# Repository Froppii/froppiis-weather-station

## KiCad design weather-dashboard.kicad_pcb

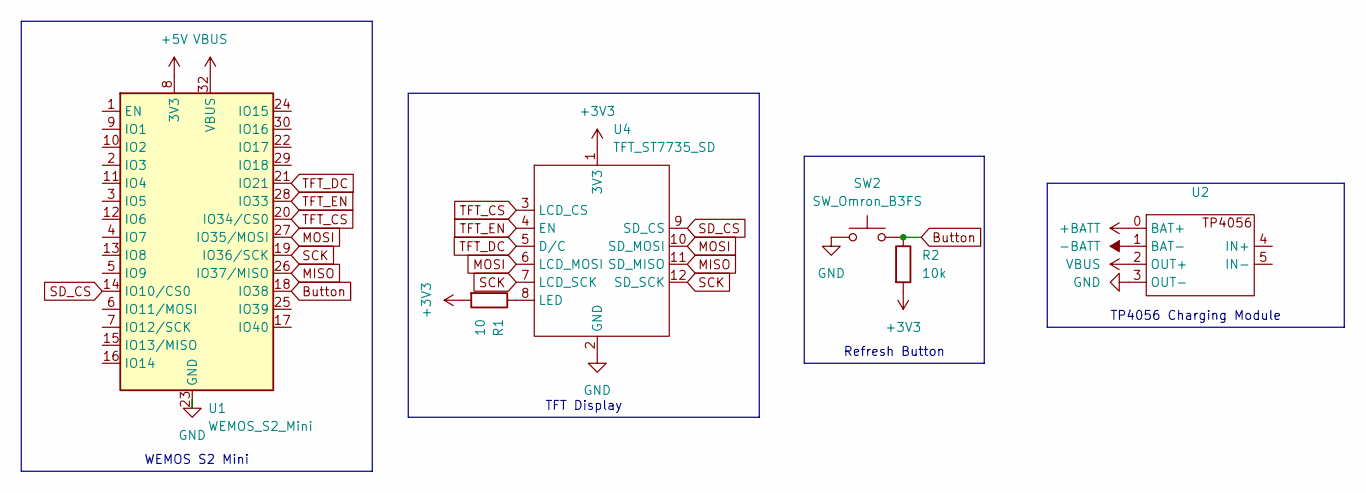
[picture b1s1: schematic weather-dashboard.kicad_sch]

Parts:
R1: 10; R_Axial_DIN0309_L9.0mm_D3.2mm_P12.70mm_Horizontal
R2: 10k; R_Axial_DIN0309_L9.0mm_D3.2mm_P12.70mm_Horizontal
SW2: SW_Omron_B3FS; SW_Tactile_Straight_KSA0Axx1LFTR
U1: WEMOS_S2_Mini
U2: TP4056
U4: TFT_ST7735_SD

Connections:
+3V3: R1.2, R2.2, U4.1 (3V3)
+5V: U1.8 (3V3)
+BATT: U2.0 (BAT+)
-BATT: U2.1 (BAT-)
Button: R2.1, SW2.2, U1.18 (IO38)
GND: SW2.1, U1.23 (GND), U2.3 (OUT-), U4.2 (GND)
MISO: U1.26 (IO37/MISO), U4.11 (SD_MISO)
MOSI: U1.27 (IO35/MOSI), U4.6 (LCD_MOSI), U4.10 (SD_MOSI)
unnamed: R1.1, U4.8 (LED)
SCK: U1.19 (IO36/SCK), U4.7 (LCD_SCK), U4.12 (SD_SCK)
SD_CS: U1.14 (IO10/CS0), U4.9 (SD_CS)
TFT_CS: U1.20 (IO34/CS0), U4.3 (LCD_CS)
TFT_DC: U1.21 (IO21), U4.5 (D/C)
TFT_EN: U1.28 (IO33), U4.4 (EN)
VBUS: U1.32 (VBUS), U2.2 (OUT+)

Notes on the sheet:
Refresh Button
TP4056 Charging Module
TFT Display
WEMOS S2 Mini

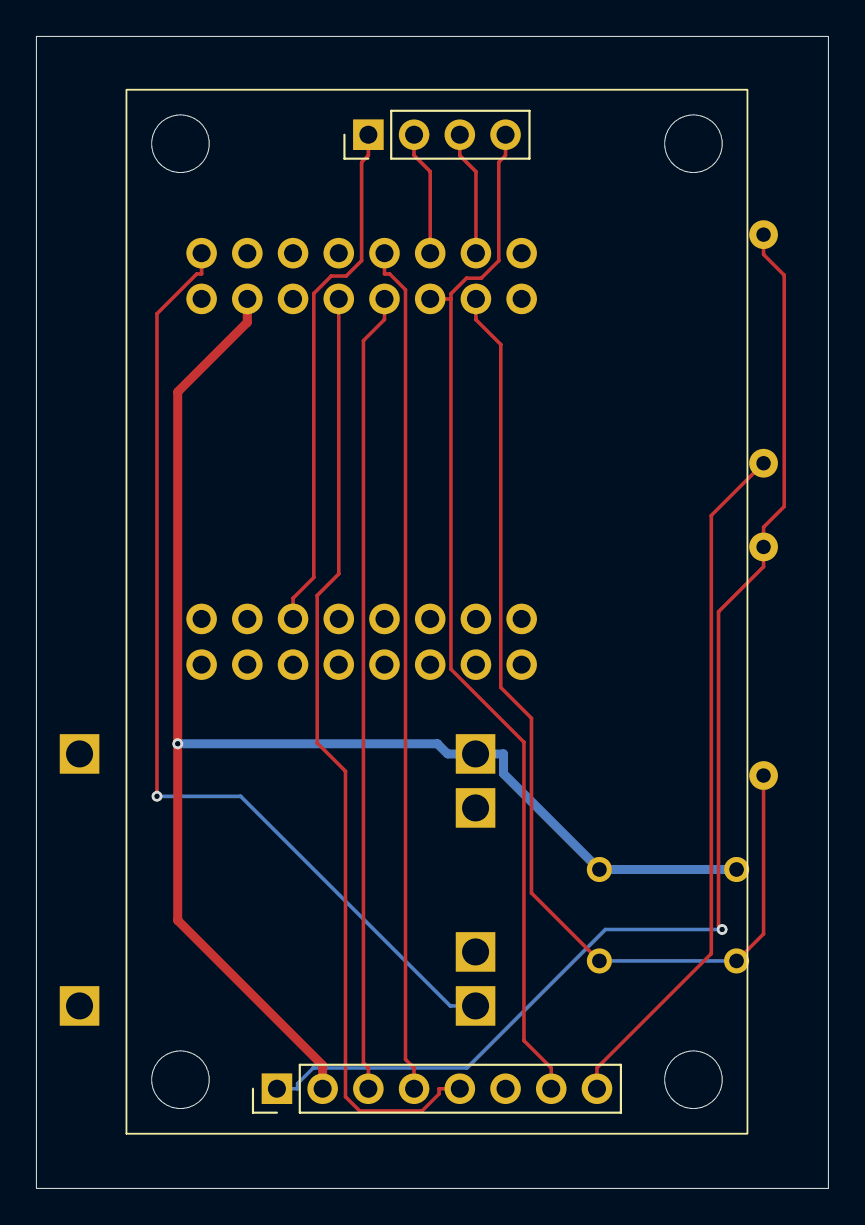
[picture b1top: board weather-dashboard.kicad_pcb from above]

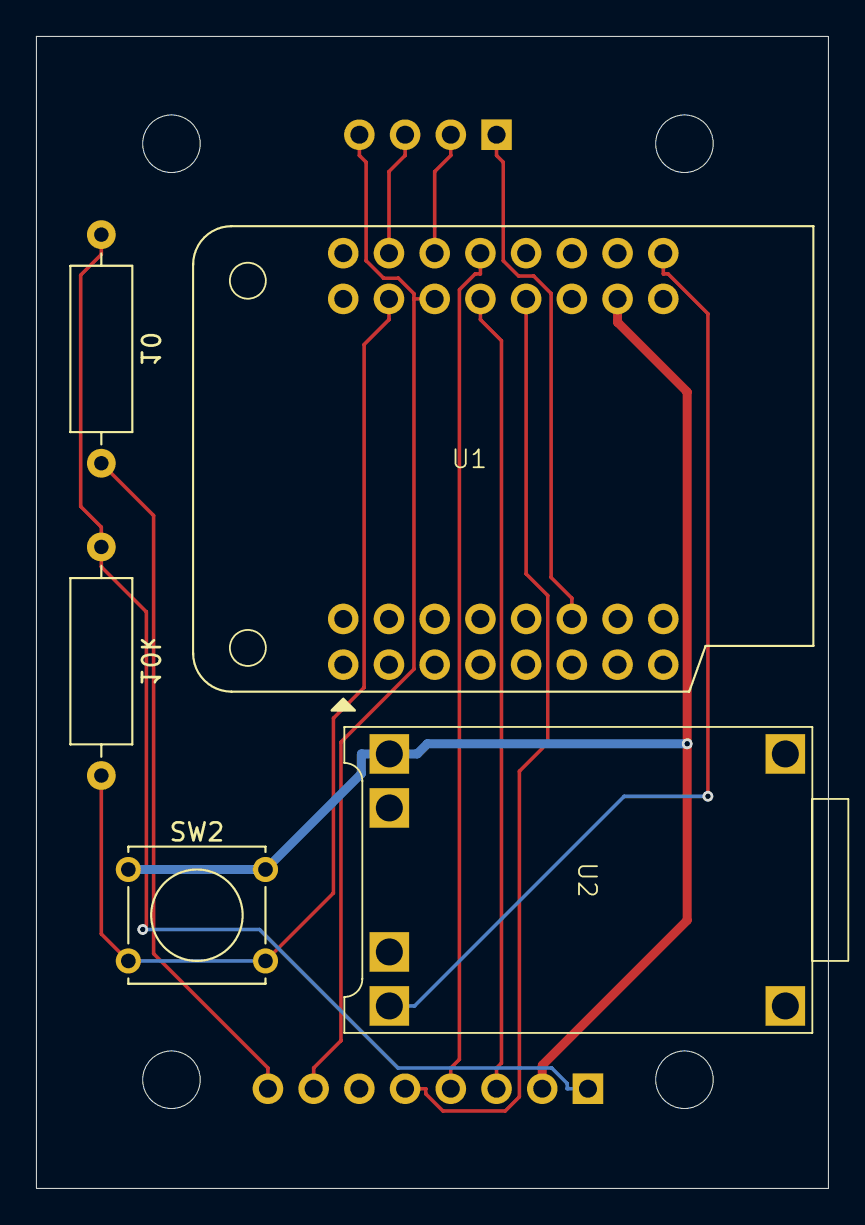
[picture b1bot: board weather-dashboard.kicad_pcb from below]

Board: 2 copper layers, 44.0 x 64.0 mm, 6 parts (5 on the bottom side), 12 nets.
